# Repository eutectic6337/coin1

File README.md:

# coin1
challenge coin with blinky lights

Feature: Using 8 PWM channels to provide dimming function for 16 LEDs
by connecting pairs in anti-parallel between a PWM pin and a GPIO.

built as a stack of 3 PCBs -
components mounted on top of bottom board,
second board has a cutout to fit a battery and for each mounted component,
and top board has holes to transmit light from LEDs

finished coin to have [relatively] smooth top and bottom

using JLCPCB's serial-number mechanism to put a unique number on each coin

Initial code flashed onto these is
[a modified version of the Arduino Blink demo](software/Blink).

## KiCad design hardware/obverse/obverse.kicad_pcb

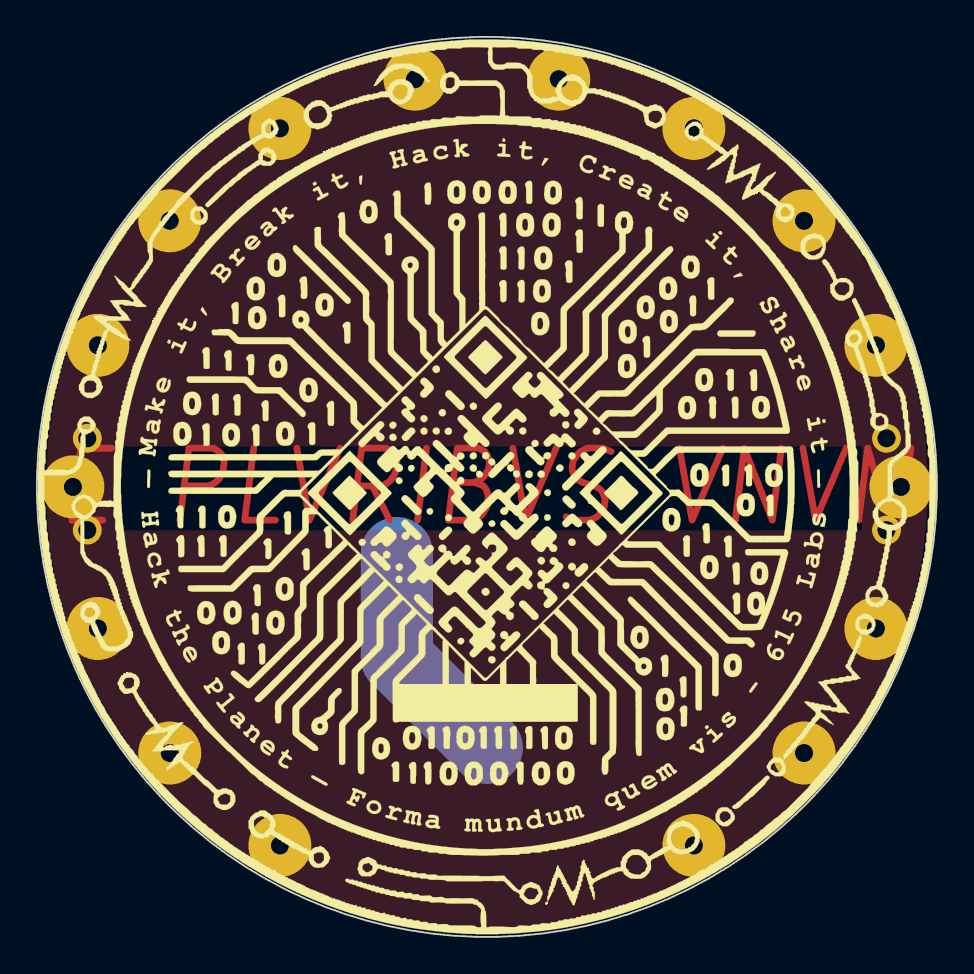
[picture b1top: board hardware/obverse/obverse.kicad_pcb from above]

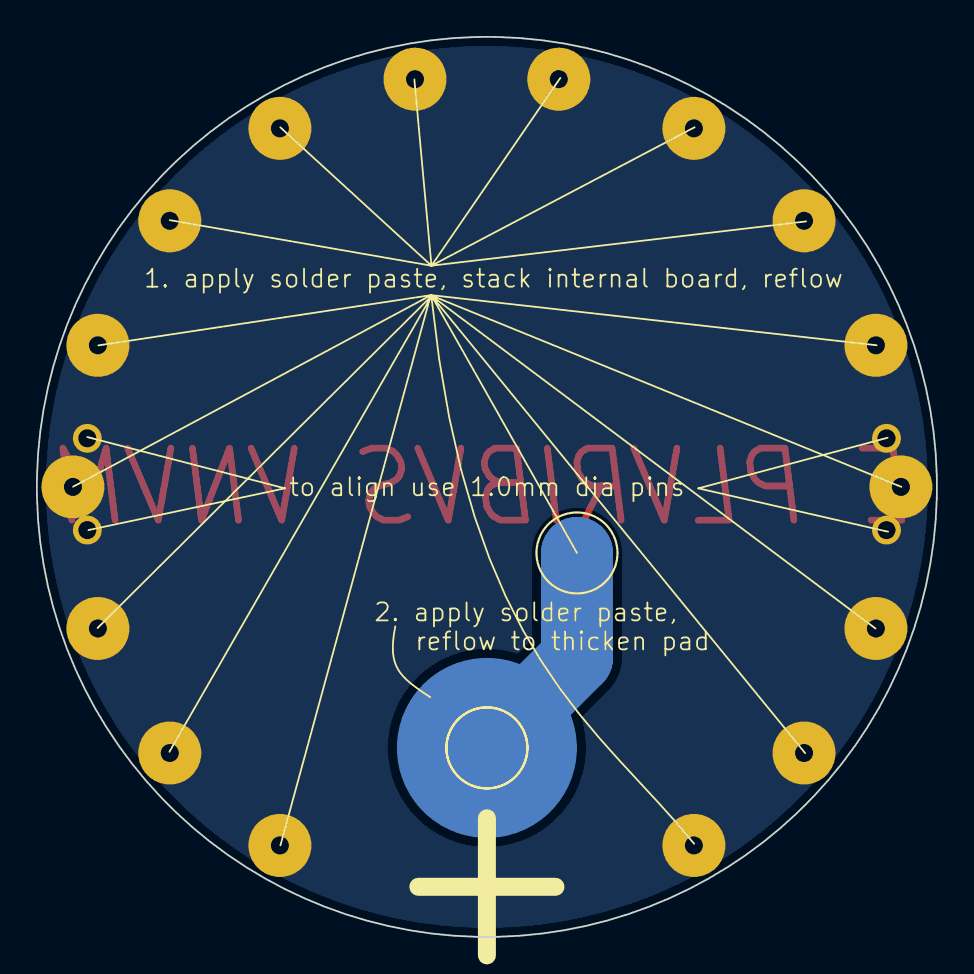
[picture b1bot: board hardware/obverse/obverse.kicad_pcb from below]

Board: 2 copper layers, 50.0 x 50.0 mm, 23 parts (3 on the bottom side), 2 nets.

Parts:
+: BAT+; TestPoint_Pad_D4.0mm
B2: BAT+; TestPoint_Pad_D4.0mm
align-o1, align-o2, align-o3, align-o4: (no value)
aperture-D1, aperture-D2, aperture-D3, aperture-D4, aperture-D5, aperture-D6, aperture-D7, aperture-D8, aperture-D9, aperture-D10, aperture-D11, aperture-D12, aperture-D13, aperture-D14, aperture-D15, aperture-D16: TestPoint_THTPad_D1.0mm_Drill0.5mm
contact-o1: TestPoint_Pad_D4.0mm

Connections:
+3V0: +.1, B2.1, contact-o1.1
GND: align-o1.1, align-o2.1, align-o3.1, align-o4.1, aperture-D1.1, aperture-D2.1, aperture-D3.1, aperture-D4.1, aperture-D5.1, aperture-D6.1, aperture-D7.1, aperture-D8.1, aperture-D9.1, aperture-D10.1, aperture-D11.1, aperture-D12.1, aperture-D13.1, aperture-D14.1, aperture-D15.1, aperture-D16.1

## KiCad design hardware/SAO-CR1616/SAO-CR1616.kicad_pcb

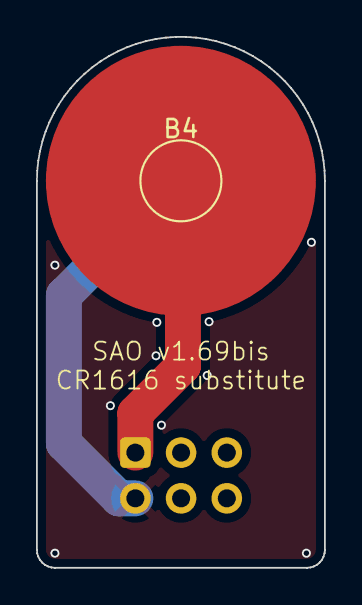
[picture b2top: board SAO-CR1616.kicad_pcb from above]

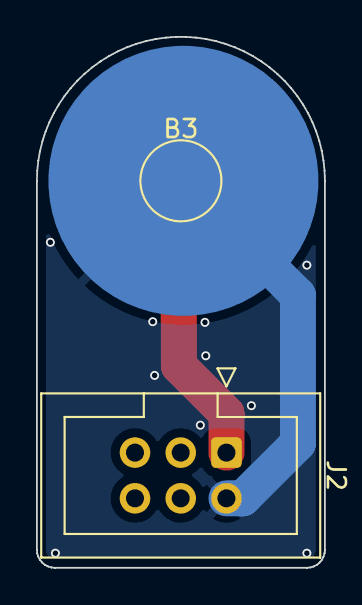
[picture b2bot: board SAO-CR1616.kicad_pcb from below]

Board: 2 copper layers, 16.0 x 29.5 mm, 5 parts (4 on the bottom side), 2 nets.

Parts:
B3: BAT-; TestPoint_Pad_D4.0mm
B4: BAT+; TestPoint_Pad_D4.0mm
J2: SAO v1.69bis addon; IDC-Header_2x03_P2.54mm_Vertical
SAO-P1, SAO-P2: (no value)

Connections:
+3V0: B4.1, J2.1 (3V3), SAO-P1.1
GND: B3.1, J2.2 (GND), SAO-P2.1

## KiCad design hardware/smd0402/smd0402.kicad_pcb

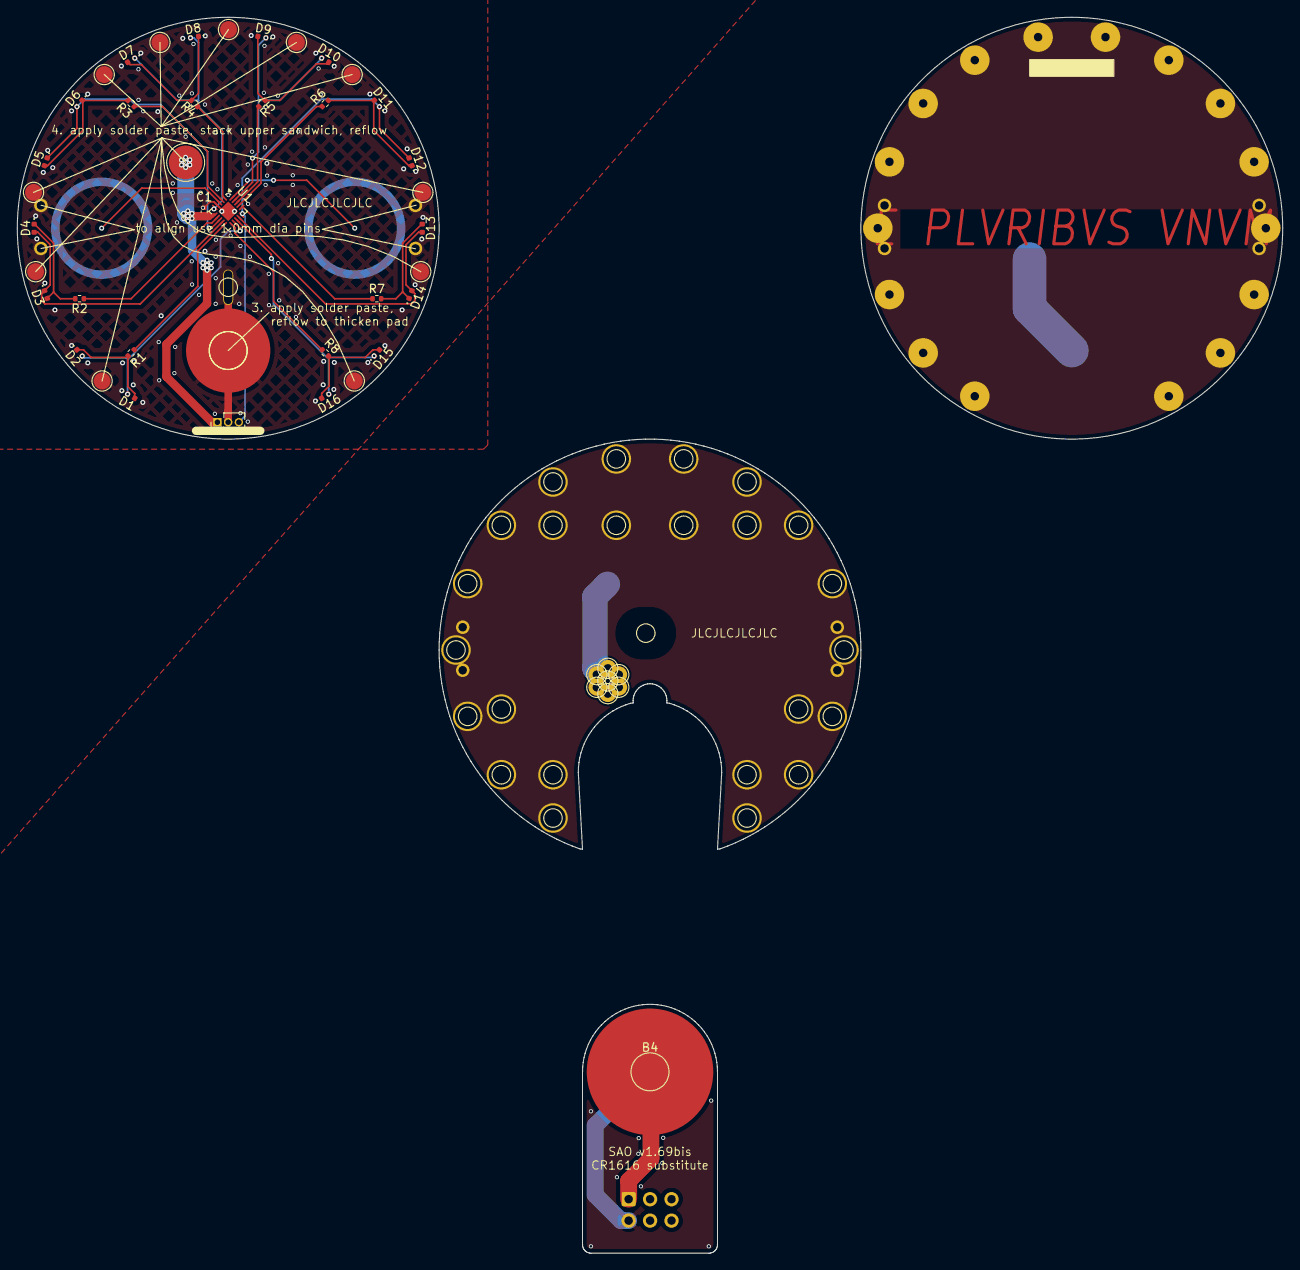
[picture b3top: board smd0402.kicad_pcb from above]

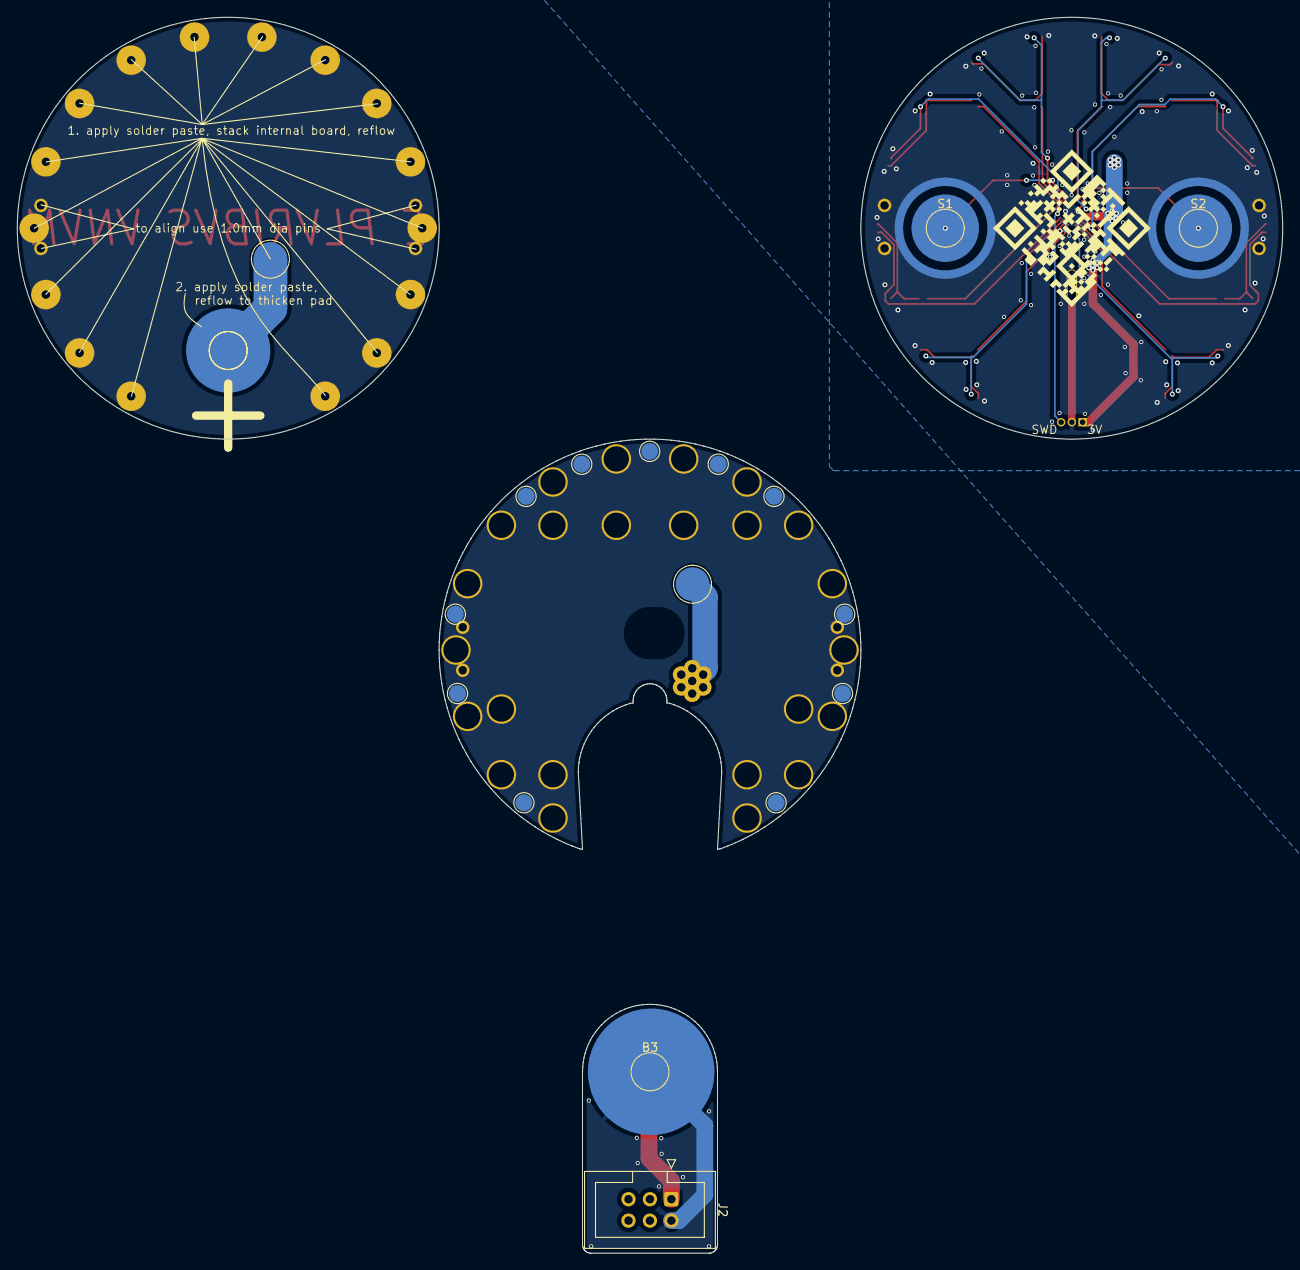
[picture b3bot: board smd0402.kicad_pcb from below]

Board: 2 copper layers, 150.0 x 146.5 mm, 124 parts (21 on the bottom side), 28 nets.

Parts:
+: BAT+; TestPoint_Pad_D4.0mm
-: BAT-; TestPoint_Pad_D4.0mm
B1, B3: BAT-; TestPoint_Pad_D4.0mm
B2, B4: BAT+; TestPoint_Pad_D4.0mm
C1: 1u; C_0402_1005Metric
D1, D2, D3, D4, D5, D6, D7, D8, D9, D10, D11, D12, D13, D14, D15, D16: LED; LED_0402_1005Metric
J1: Conn_01x03; PinHeader_1x03_P1.27mm_Vertical
J2: SAO v1.69bis addon; IDC-Header_2x03_P2.54mm_Vertical
R1, R2, R3, R4, R5, R6, R7, R8: 47R; R_0402_1005Metric
S1, S2: touch; TestPoint_Pad_D4.0mm
SAO-P1, SAO-P2: (no value)
U1: WCH CH32V003F4U6; QFN-20-1EP_3x3mm_P0.4mm_EP1.65x1.65mm
align-i1, align-i2, align-i3, align-i4: (no value)
align-o1, align-o2, align-o3, align-o4: (no value)
align-r1, align-r2, align-r3, align-r4: (no value)
aperture-D1, aperture-D2, aperture-D3, aperture-D4, aperture-D5, aperture-D6, aperture-D7, aperture-D8, aperture-D9, aperture-D10, aperture-D11, aperture-D12, aperture-D13, aperture-D14, aperture-D15, aperture-D16: TestPoint_THTPad_D1.0mm_Drill0.5mm
battery-eject1: TestPoint_THTPad_3.0x3.0mm_Drill1.5mm
clearance-D1, clearance-D2, clearance-D3, clearance-D4, clearance-D5, clearance-D6, clearance-D7, clearance-D8, clearance-D9, clearance-D10, clearance-D11, clearance-D12, clearance-D13, clearance-D14, clearance-D15, clearance-D16: TestPoint_THTPad_3.0x3.0mm_Drill1.5mm
clearance-R1, clearance-R2, clearance-R3, clearance-R4, clearance-R5, clearance-R6, clearance-R7, clearance-R8: TestPoint_THTPad_3.0x3.0mm_Drill1.5mm
clearance-U1: TestPoint_THTPad_3.0x3.0mm_Drill1.5mm
contact-i1: TestPoint_Pad_D4.0mm
contact-o1: TestPoint_Pad_D4.0mm
contact-r1: TestPoint_Pad_D4.0mm
stitch1, stitch1#2, stitch1#3, stitch1#4, stitch1#5, stitch1#6, stitch1#7, stitch1#8, stitch1#9, stitch1#10, stitch1#11, stitch2, stitch2#2, stitch2#3, stitch2#4, stitch2#5, stitch2#6, stitch2#7, stitch2#8, stitch2#9, stitch2#10, stitch2#11: TestPoint_Pad_D2.0mm
through-i1, through-i2, through-i3, through-i4, through-i5, through-i6, through-i7: TestPoint_THTPad_D2.0mm_Drill1.0mm

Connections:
+3V0: +.1, B2.1, B4.1, C1.1, J1.1, J2.1 (3V3), SAO-P1.1, U1.6 (VDD), contact-i1.1, contact-o1.1, contact-r1.1, through-i1.1, through-i2.1, through-i3.1, through-i4.1, through-i5.1, through-i6.1, through-i7.1
/touch1: S1.1, U1.20 (ADC_IN6)
/touch2: S2.1, U1.3 (ADC_IN0)
GND: -.1, B1.1, B3.1, C1.2, J1.2, J2.2 (GND), SAO-P2.1, U1.4 (VSS), U1.21 (VSS), align-i1.1, align-i2.1, align-i3.1, align-i4.1, align-o1.1, align-o2.1, align-o3.1, align-o4.1, align-r1.1, align-r2.1, align-r3.1, align-r4.1, aperture-D1.1, aperture-D2.1, aperture-D3.1, aperture-D4.1, aperture-D5.1, aperture-D6.1, aperture-D7.1, aperture-D8.1, aperture-D9.1, aperture-D10.1, aperture-D11.1, aperture-D12.1, aperture-D13.1, aperture-D14.1, aperture-D15.1, aperture-D16.1, battery-eject1.1, clearance-D1.1, clearance-D2.1, clearance-D3.1, clearance-D4.1, clearance-D5.1, clearance-D6.1, clearance-D7.1, clearance-D8.1, clearance-D9.1, clearance-D10.1, clearance-D11.1, clearance-D12.1, clearance-D13.1, clearance-D14.1, clearance-D15.1, clearance-D16.1, stitch1.1, stitch1#2.1, stitch1#3.1, stitch1#4.1, stitch1#5.1, stitch1#6.1, stitch1#7.1, stitch1#8.1, stitch1#9.1, stitch1#10.1, stitch1#11.1, stitch2.1, stitch2#2.1, stitch2#3.1, stitch2#4.1, stitch2#5.1, stitch2#6.1, stitch2#7.1, stitch2#8.1, stitch2#9.1, stitch2#10.1, stitch2#11.1
GP1: D1.1 (K), D2.2 (A), U1.12 (PC5)
GP2: D3.1 (K), D4.2 (A), U1.9 (PC2)
GP3: D5.1 (K), D6.2 (A), U1.8 (PC1)
GP4: D7.1 (K), D8.2 (A), U1.5 (PD0)
GP5: D9.1 (K), D10.2 (A), U1.19 (PD5)
GP6: D11.1 (K), D12.2 (A), J1.3, U1.15 (SWIO)
GP7: D13.1 (K), D14.2 (A), U1.14 (PC7)
GP8: D15.1 (K), D16.2 (A), U1.13 (PC6)
unnamed: D1.2 (A), D2.1 (K), R1.2
unnamed: D3.2 (A), D4.1 (K), R2.2
unnamed: D5.2 (A), D6.1 (K), R3.2
unnamed: D7.2 (A), D8.1 (K), R4.2
unnamed: D9.2 (A), D10.1 (K), R5.2
unnamed: D11.2 (A), D12.1 (K), R6.2
unnamed: D13.2 (A), D14.1 (K), R7.2
unnamed: D15.2 (A), D16.1 (K), R8.2
PWM1: R1.1, U1.10 (TIM1_CH3)
PWM2: R2.1, U1.7 (TIM2_CH3)
PWM3: R3.1, U1.2 (TIM1_CH2)
PWM4: R4.1, U1.1 (TIM2_CH4)
PWM5: R5.1, U1.18 (TIM2_CH1)
PWM6: R6.1, U1.17 (TIM2_CH2)
PWM7: R7.1, U1.16 (TIM1_CH1)
PWM8: R8.1, U1.11 (TIM1_CH4)

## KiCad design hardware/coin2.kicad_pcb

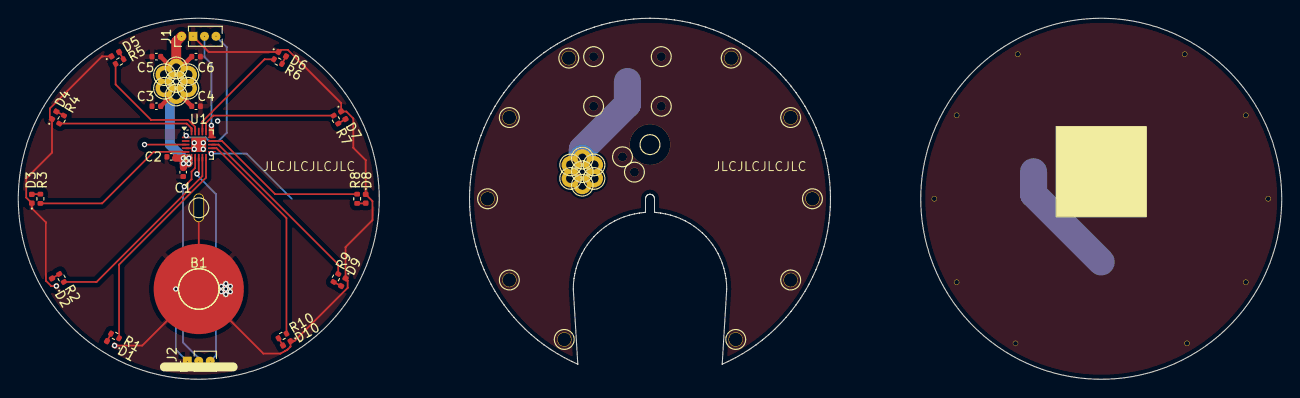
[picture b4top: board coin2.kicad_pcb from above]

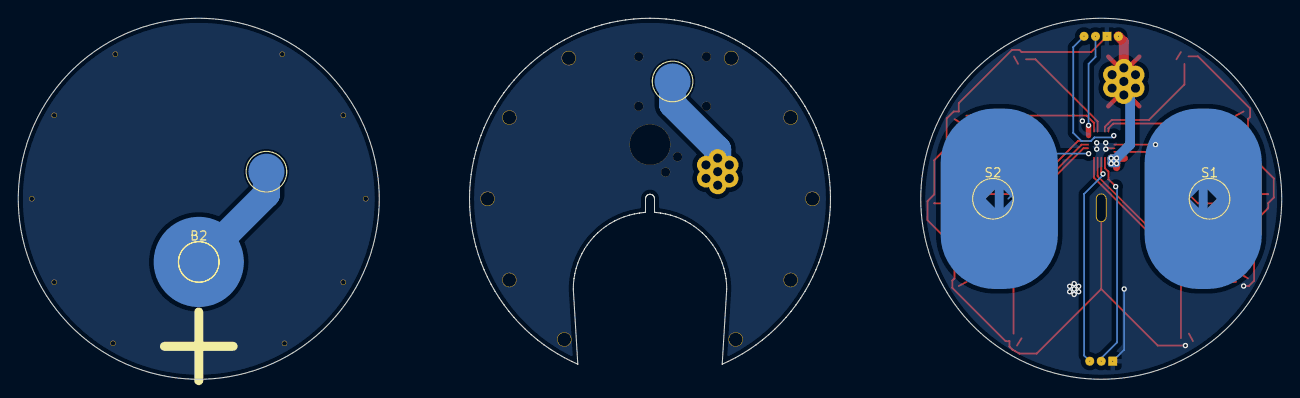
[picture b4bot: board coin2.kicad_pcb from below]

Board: 2 copper layers, 140.0 x 40.0 mm, 77 parts (4 on the bottom side), 28 nets.

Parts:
+: BAT+; TestPoint_Pad_D4.0mm
-: BAT-; TestPoint_Pad_D4.0mm
B1: BAT-; TestPoint_Pad_D4.0mm
B2: BAT+; TestPoint_Pad_D4.0mm
C1, C2, C3, C4, C5, C6: 10n; C_0402_1005Metric
D1, D2, D3, D4, D5, D6, D7, D8, D9, D10: LED; LED_0402_1005Metric
J1: Conn_01x04; PinHeader_1x04_P1.27mm_Vertical
J2: Conn_01x03; PinHeader_1x03_P1.27mm_Vertical
R1, R2, R3, R4, R5, R6, R7, R8, R9, R10: 47R; R_0402_1005Metric
S1, S2: touch; TestPoint_Pad_D4.0mm
T1, T1#2, T12, T13, T14, T15, T16, T18, T19, T20, T21, T21#2, T21#3, T21#4, T21#5, T21#6, T21#7, T22: TestPoint_THTPad_3.0x3.0mm_Drill1.5mm
T42, T43, T44, T45, T46, T48, T49, T50, T51, T52#3: TestPoint_THTPad_D1.0mm_Drill0.5mm
T51#2, T51#3, T51#4, T51#5, T52, T52#2, T53, T53#2, T54, T54#2, T55, T55#2, T56, T56#2: TestPoint_THTPad_D2.0mm_Drill1.0mm
U1: WCH CH32V003F4U6; QFN-20-1EP_3x3mm_P0.4mm_EP1.65x1.65mm

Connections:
+3V0: +.1, B2.1, C1.1, C2.1, C3.1, C4.1, C5.1, C6.1, J1.1, T51#2.1, T51#3.1, T51#4.1, T51#5.1, T52.1, T52#2.1, T53.1, T53#2.1, T54.1, T54#2.1, T55.1, T55#2.1, T56.1, T56#2.1, U1.6 (VDD)
/LED1: R1.1, U1.10 (PC3)
/LED2: R2.1, U1.9 (PC2)
/LED3: R3.1, U1.5 (PD0)
/LED4: R4.1, U1.20 (PD6)
/LED5: R5.1, U1.19 (PD5)
/LED6: R6.1, U1.17 (PD3)
/LED7: R7.1, U1.16 (PD2)
/LED8: R8.1, U1.14 (PC7)
/LED9: R9.1, U1.13 (PC6)
/LED10: R10.1, U1.12 (PC5)
/NRST: J1.4, U1.1 (NRST)
/RX: J2.3, U1.8 (USART_RX_3)
/SWIO: J1.3, U1.15 (SWIO)
/TX: J2.2, U1.7 (USART_TX_3)
/touch1: S1.1, U1.3 (ADC_IN0)
/touch2: S2.1, U1.11 (ADC_IN2)
GND: -.1, B1.1, C1.2, C2.2, C3.2, C4.2, C5.2, C6.2, D1.1 (K), D2.1 (K), D3.1 (K), D4.1 (K), D5.1 (K), D6.1 (K), D7.1 (K), D8.1 (K), D9.1 (K), D10.1 (K), J1.2, J2.1, T1.1, T1#2.1, T12.1, T13.1, T14.1, T15.1, T16.1, T18.1, T19.1, T20.1, T21.1, T21#2.1, T21#3.1, T21#4.1, T21#5.1, T21#6.1, T21#7.1, T22.1, T42.1, T43.1, T44.1, T45.1, T46.1, T48.1, T49.1, T50.1, T51.1, T52#3.1, U1.4 (VSS)
unnamed: D1.2 (A), R1.2
unnamed: D2.2 (A), R2.2
unnamed: D3.2 (A), R3.2
unnamed: D4.2 (A), R4.2
unnamed: D5.2 (A), R5.2
unnamed: D6.2 (A), R6.2
unnamed: D7.2 (A), R7.2
unnamed: D8.2 (A), R8.2
unnamed: D9.2 (A), R9.2
unnamed: D10.2 (A), R10.2

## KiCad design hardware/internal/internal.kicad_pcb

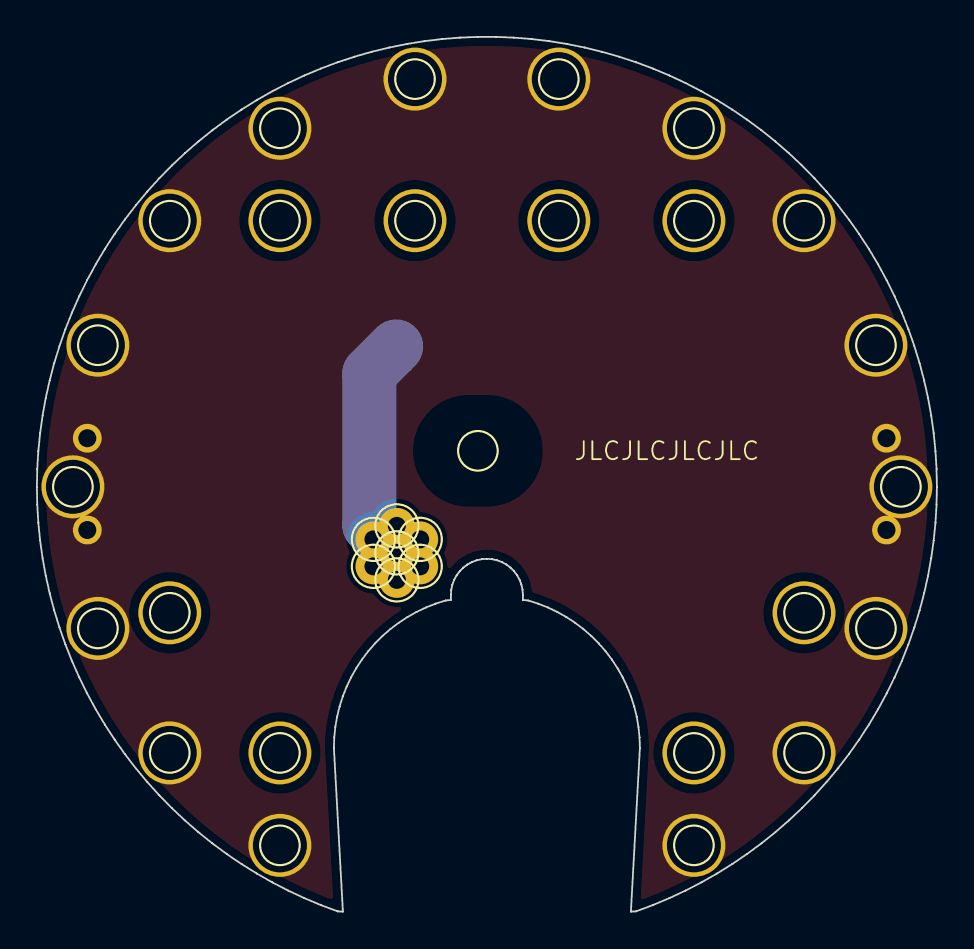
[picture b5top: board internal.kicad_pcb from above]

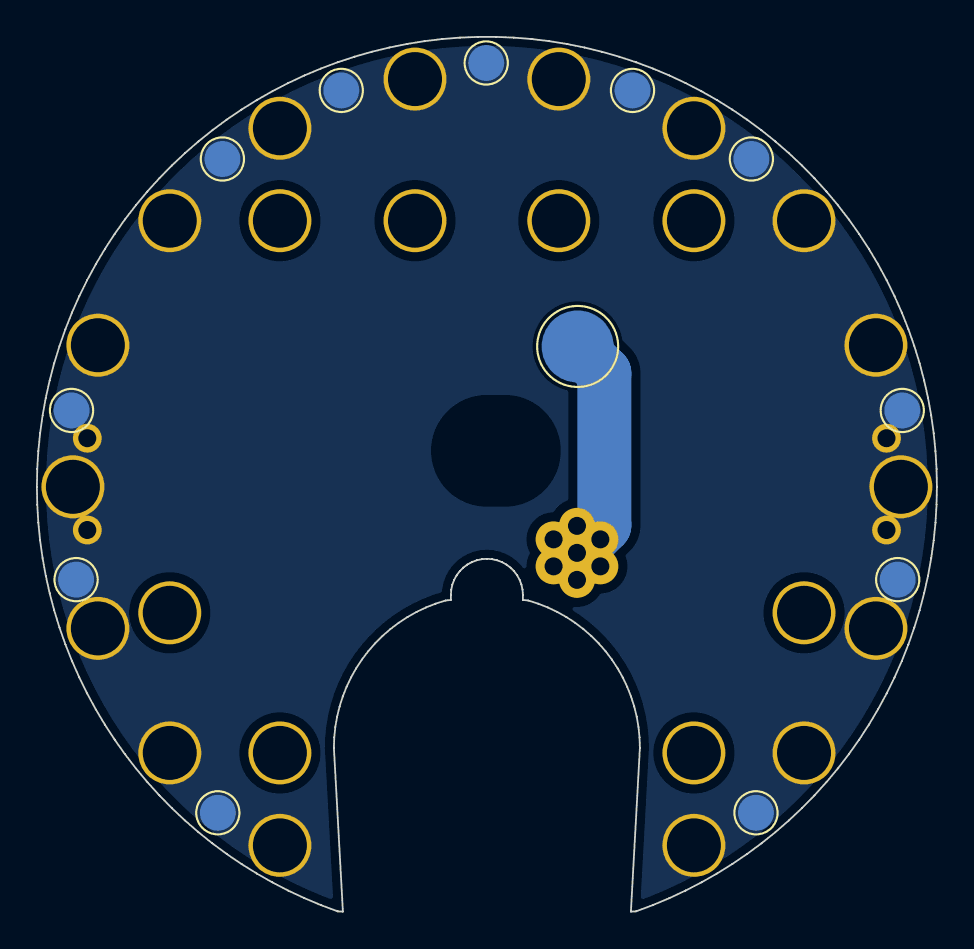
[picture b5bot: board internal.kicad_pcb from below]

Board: 2 copper layers, 50.0 x 48.6 mm, 48 parts (12 on the bottom side), 2 nets.

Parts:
align-i1, align-i2, align-i3, align-i4: (no value)
clearance-D1, clearance-D2, clearance-D3, clearance-D4, clearance-D5, clearance-D6, clearance-D7, clearance-D8, clearance-D9, clearance-D10, clearance-D11, clearance-D12, clearance-D13, clearance-D14, clearance-D15, clearance-D16: TestPoint_THTPad_3.0x3.0mm_Drill1.5mm
clearance-R1, clearance-R2, clearance-R3, clearance-R4, clearance-R5, clearance-R6, clearance-R7, clearance-R8: TestPoint_THTPad_3.0x3.0mm_Drill1.5mm
clearance-U1: TestPoint_THTPad_3.0x3.0mm_Drill1.5mm
contact-i1: TestPoint_Pad_D4.0mm
stitch2, stitch2#2, stitch2#3, stitch2#4, stitch2#5, stitch2#6, stitch2#7, stitch2#8, stitch2#9, stitch2#10, stitch2#11: TestPoint_Pad_D2.0mm
through-i1, through-i2, through-i3, through-i4, through-i5, through-i6, through-i7: TestPoint_THTPad_D2.0mm_Drill1.0mm

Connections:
+3V0: contact-i1.1, through-i1.1, through-i2.1, through-i3.1, through-i4.1, through-i5.1, through-i6.1, through-i7.1
GND: align-i1.1, align-i2.1, align-i3.1, align-i4.1, clearance-D1.1, clearance-D2.1, clearance-D3.1, clearance-D4.1, clearance-D5.1, clearance-D6.1, clearance-D7.1, clearance-D8.1, clearance-D9.1, clearance-D10.1, clearance-D11.1, clearance-D12.1, clearance-D13.1, clearance-D14.1, clearance-D15.1, clearance-D16.1, stitch2.1, stitch2#2.1, stitch2#3.1, stitch2#4.1, stitch2#5.1, stitch2#6.1, stitch2#7.1, stitch2#8.1, stitch2#9.1, stitch2#10.1, stitch2#11.1

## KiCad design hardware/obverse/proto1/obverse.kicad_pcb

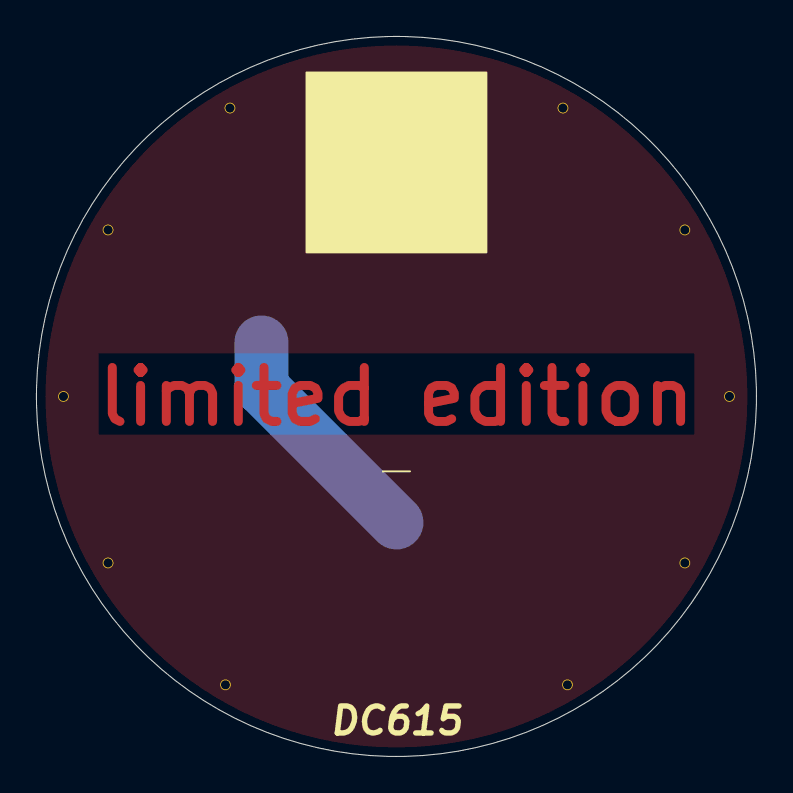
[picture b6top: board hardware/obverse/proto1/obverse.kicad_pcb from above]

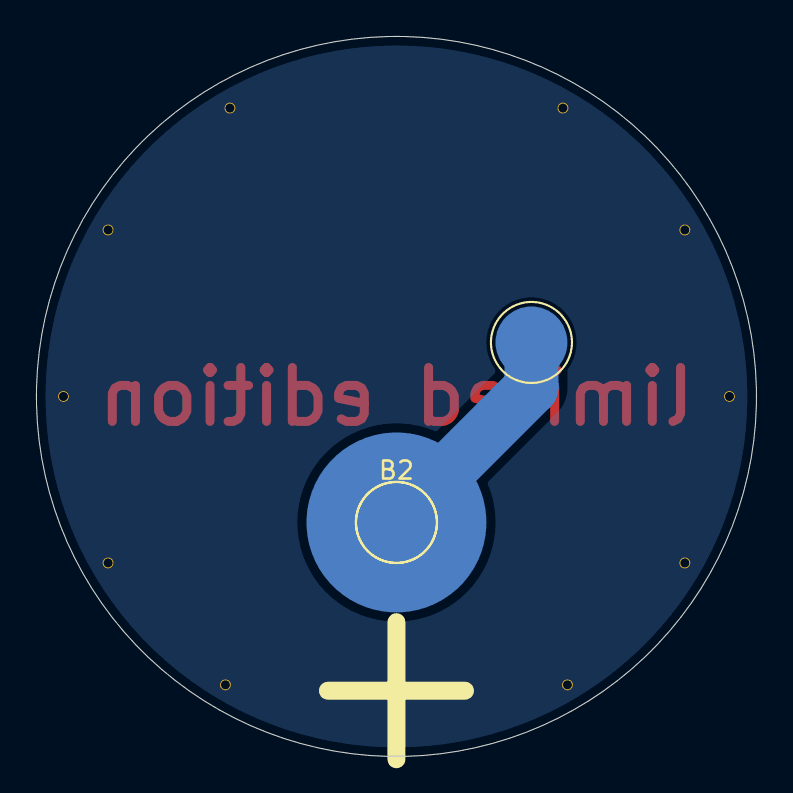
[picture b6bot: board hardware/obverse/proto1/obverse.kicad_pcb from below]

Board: 2 copper layers, 40.0 x 40.0 mm, 12 parts (2 on the bottom side), 2 nets.

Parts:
+: BAT+; TestPoint_Pad_D4.0mm
B2: BAT+; TestPoint_Pad_D4.0mm
T42, T43, T44, T45, T46, T48, T49, T50, T51, T52: TestPoint_THTPad_D1.0mm_Drill0.5mm

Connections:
+3V0: +.1, B2.1
GND: T42.1, T43.1, T44.1, T45.1, T46.1, T48.1, T49.1, T50.1, T51.1, T52.1

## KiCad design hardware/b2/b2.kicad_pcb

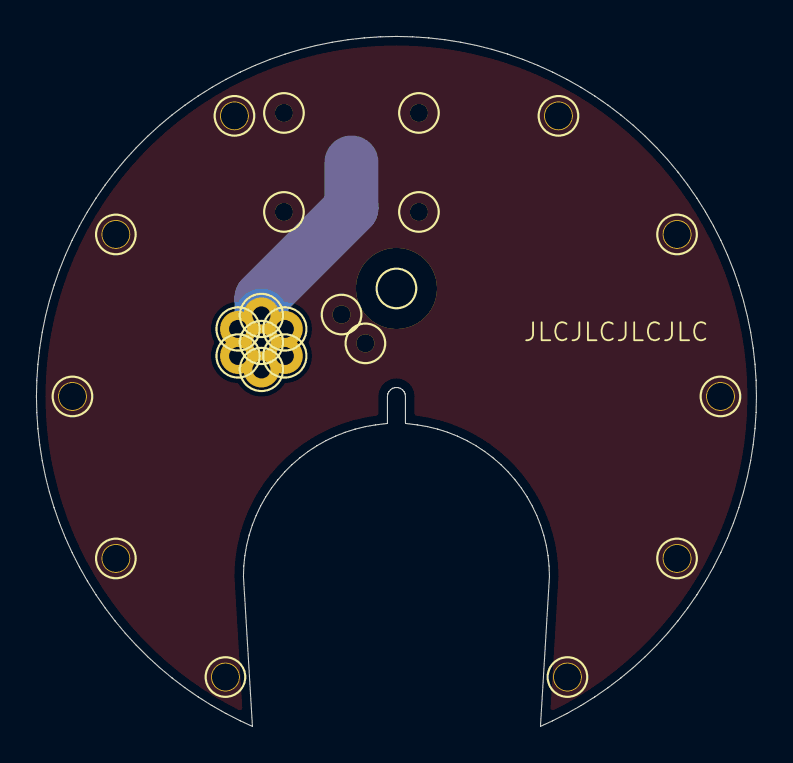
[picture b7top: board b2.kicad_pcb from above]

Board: 2 copper layers, 40.0 x 38.3 mm, 24 parts (0 on the bottom side), 2 nets.

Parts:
T1, T12, T13, T14, T15, T16, T18, T19, T20, T21, T21#2, T21#3, T21#4, T21#5, T21#6, T21#7, T22: TestPoint_THTPad_3.0x3.0mm_Drill1.5mm
T51, T51#2, T52, T53, T54, T55, T56: TestPoint_THTPad_D2.0mm_Drill1.0mm

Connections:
+3V0: T51.1, T51#2.1, T52.1, T53.1, T54.1, T55.1, T56.1
GND: T1.1, T12.1, T13.1, T14.1, T15.1, T16.1, T18.1, T19.1, T20.1, T21.1, T21#2.1, T21#3.1, T21#4.1, T21#5.1, T21#6.1, T21#7.1, T22.1

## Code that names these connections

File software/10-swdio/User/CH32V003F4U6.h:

/*
 * CH32V003F4U6.h
 *
 *  Created on: Apr 29, 2025
 *      Author: mlp
 */

#ifndef USER_CH32V003F4U6_H_
#define USER_CH32V003F4U6_H_

#define PD7 1
#define PA1 2
#define PA2 3
#define VSS 4
#define PD0 5
#define VDD 6
#define PC0 7
#define PC1 8
#define PC2 9
#define PC3 10
#define PC4 11
#define PC5 12
#define PC6 13
#define PC7 14
#define PD1 15
#define PD2 16
#define PD3 17
#define PD4 18
#define PD5 19
#define PD6 20

#if REMAP == 00
#define UCK	PD4
#define A7	PD4
#define OPO	PD4
#define TIM2_ETR	PD4

#define UTX	PD5
#define A5	PD5
#define URX	PD6
#define A6	PD6

#define NRST	PD7
#define OPP1	PD7

#define A1	PA1
#define OPN0	PA1

#define A0	PA2
#define OPP0	PA2
#define TIM1_CH2N	PA2

#define OPN1	PD0
#define TIM1_CH1N	PD0

#define SDA	PC1
#define NSS	PC1

#define SCL	PC2
#define URTS	PC2
#define TIM1_BKIN	PC2

#define MCO	PC4
#define A2	PC4

#define SCK	PC5
#define TIM1_ETR	PC5

#define MOSI	PC6
#define MISO	PC7

#define SWIO	PD1
#define TIM1_CH3N	PD1
#define AETR2	PD1

#define A3	PD2

#define A4	PD3
#define AETR	PD3
#define UCTS	PD3

#define TIM1_CH1	PD2
#define TIM1_CH2	PA1
#define TIM1_CH3	PC3
#define TIM1_CH4	PC4

#define TIM2_CH1	PD4
#define TIM2_CH2	PD3
#define TIM2_CH3	PC0
#define TIM2_CH4	PD7

#elif REMAP == 01
#define TIM1_CH1	PC6
#define TIM1_CH2	PC7
#define TIM1_CH3	PC0
#define TIM1_CH4	PD3

#define TIM2_CH1	PC5
#define TIM2_CH2	PC2
#define TIM2_CH3	PD2
#define TIM2_CH4	PC1

#elif REMAP == 10
#define TIM1_CH1	PD2
#define TIM1_CH2	PA1
#define TIM1_CH3	PC3
#define TIM1_CH4	PC4

#define TIM2_CH1	PC1
#define TIM2_CH2	PD3
#define TIM2_CH3	PC0
#define TIM2_CH4	PD7

#elif REMAP == 11
#define TIM1_CH1	PC4
#define TIM1_CH2	PC7
#define TIM1_CH3	PC5
#define TIM1_CH4	PD4

#define TIM2_CH1	PC1
#define TIM2_CH2	PC7
#define TIM2_CH3	PD6
#define TIM2_CH4	PD5

#else
#error bad REMAP
#endif

#endif /* USER_CH32V003F4U6_H_ */

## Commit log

2024-12-03 add locations for JLCPCB order IDs
2024-12-03 add LCSC part details
2024-12-03 use pin headers for their pads only
2024-12-03 made a version with 0402 rather than 0201 R&D
2024-12-03 route and DRC the new board
2024-12-04 cleanup some hole locations etc.
2024-12-04 add bypass caps, tweak clearance holes
2024-12-05 change connectors from 2.54 to 1.27mm spacing, add decoupling
2024-12-05 separate models and make explicit
2024-12-05 improve DRC
2024-12-05 separate boards, generate fab output
2024-12-05 allow CSVs
2024-12-05 adjust BOM+POS files for JLCPCB
2024-12-05 add LIMITED EDITION text
2024-12-05 make LIMITED EDITION be bare copper
2024-12-05 update fab output
2024-12-05 create QR codes pointing to this repo
2024-12-05 add description
2024-12-05 add repo URL QR on back, tweak text on front
2024-12-05 tweak toward JLC assembly files
2024-12-05 refreshed fab files
2024-12-05 convert KiCad to JLC format
2024-12-05 forgot to nuke unplaced jumpers
2024-12-05 and nuke unused column
2025-01-08 blink 2 LEDs on eval board
2025-01-10 use PD3 for LED, free up PD1 for debug interface
2025-01-10 missed a pin
2025-01-10 also missed initialising GPIOC clock - now it blinks
2025-01-15 use PC3,PC2 = LED1,LED2 on coin
2025-01-15 add coin-chase project
2025-01-15 and rename it
2025-01-15 finish the rename
2025-01-15 ignore packaged fab files
2025-01-15 chase 10 LEDs around the coin
2025-01-17 cleaned up horrible code
2025-01-17 start to make configurable patterns
2025-01-17 new skeleton
2025-01-17 finish the project-rename operation
2025-01-17 Revert "finish the project-rename operation"
    This reverts commit 6e46c28f29a582f192df99f92211d17d19c75442.
2025-01-17 and nuke it
2025-01-18 skeleton for pattern sequence
2025-01-18 add PWM
2025-01-22 [start to] take into account PWM-channel overlaps
2025-01-22 finished pin selection
2025-01-22 add Alchemmer's bunch-o-patterns
2025-01-22 turn on Timer 2's clock
2025-01-22 more cleanup
2025-01-22 add macro to select sequence
2025-02-03 eclipse prefs
2025-02-03 moved clearance holes to match decoupling caps
2025-02-04 reassign touch pads to OPNx
2025-02-04 look long and hard at LED-driving pins
2025-02-04 reassign pins for LEDs and touchpads
2025-02-04 change bypass caps from 10n to 1u
2025-02-06 add some docs on GPIO remapping
2025-02-06 lose NRST, use TIM2 default mapping
2025-02-06 re-route a couple LED signals
2025-02-06 tweak pin allocations
2025-02-12 add some used pins
2025-02-14 boost dia to 50mm, use back-to-back LEDs, add SAO
2025-02-14 document back-to-back LEDs
2025-02-15 clean up DRC
2025-02-15 add via-stitching
2025-02-15 final DRC cleanup
2025-02-16 regenerated repo QR code
2025-02-16 separate boards and generate fab files
2025-02-16 blink a different pair of LEDs
2025-02-16 add diagnostic output
2025-02-16 tweak text out
2025-02-16 verify that what we want the coin to do, it will be able to
2025-02-16 add comments; drop in timer interrupt handler
2025-02-16 use SysTick interrupt to keep time
2025-02-16 convert line endings to all LF
2025-02-16 move defines near to SysTick code
2025-02-16 remove Delay calls
2025-02-17 make clock work(ish)
2025-02-17 make explicit "wait" wrappers
2025-02-22 make inline functions ISO rather than K&R (or C++)
2025-02-22 split main.c into modules
2025-02-22 tweak compiler warning and other options
2025-02-22 rename functions to match files
2025-02-22 start making config switchable
2025-02-22 include prereq header
2025-02-22 call SystemInit()
2025-02-22 add DEBUG build config
2025-02-22 cleanse DEBUG behaviour
2025-02-22 delay before first print, and add blank line
2025-02-22 misc project tweaks
2025-02-22 create ch32fun version of validator
2025-02-22 silence a couple warnings
2025-02-23 further tweaks to get ch32fun project (validate2) to build
2025-02-26 convert to Kicad 9
2025-02-26 add SAO display board
2025-02-26 created board
2025-02-26 added power bypass caps
2025-02-26 separate into fab-able parts
2025-02-26 update fab files
2025-02-26 remove 4 bogus segments from edge cuts
2025-02-26 render boards
2025-02-26 regenerate fab files
2025-02-26 because I moved some text
2025-02-26 regen fab files
2025-02-27 make mousebite holes 0.3mm
2025-02-27 panelize for assembly
2025-04-29 new sample code: first, use SWD for IO
2025-04-29 nuked and recreated
2025-04-29 Eclipse build-parser treats "remove unused section" diagnostic as error?!
2025-04-29 remove "-v" from build stages
2025-04-29 remove link-time extra verbose output
2025-04-29 eliminate format warnings
2025-04-29 enable SWD debug printf
2025-04-29 annotate 2 warnings
2025-04-29 remove calls to USART code
2025-04-29 add ID comment
2025-04-30 define pins
2025-04-30 add pattern-handler
2025-05-20 rename to reflect functionality
2025-05-20 change 'set()/clr()' interface to 'set(val)'
2025-05-21 parameterize pins
2025-05-21 graft in time-handling from ch32fun; also, add assert()s
2025-05-21 cleanup, document
2025-05-21 cleanup
2025-05-22 replace switch/case with table lookup
2025-05-22 extract chip-specific code
2025-05-22 reduce coupling, remove dummy array element
2025-05-22 simplify pin spec
2025-06-03 hash area fill; un-plate MCU clearance hole
2025-06-03 add struct tag
2025-06-09 shrink touchpad to 8mm circle
2025-06-12 add 2 alignment holes to each outer layer
2025-06-12 remove SAO display
2025-06-12 cleanup fab files
2025-06-13 change text
2025-06-13 reduce maskless copper; tweak font
2025-06-13 cleaned up pads; relocated repo QR
2025-06-13 saved
2025-06-13 ready to panelize 4 reverse boards
2025-06-13 integrated final assembly instructions
2025-06-13 tweak instructions
2025-06-13 update rails+mousebites empty panel
2025-06-13 separate boards
2025-06-13 automagic project file updates
2025-06-13 rebuild panel with all SWD ports toward outside
2025-06-14 make clearance-holes less likely to contact
2025-06-14 add SVGs of Alchemmer's artwork
2025-06-15 update parts to those in stock at JLC *now*
2025-06-15 separate sandwich layers to generate fab files
2025-06-15 add reference URL
2025-06-15 add tooling holes; relocate fiducials
2025-06-16 add tooling holes; relocate fiducials; cleanup
2025-06-16 start to panelize reverse layer
2025-06-16 finish panelization
2025-06-17 try lower-poly reverse artwork
2025-06-24 make eject-slot NPTH
2025-06-24 add polarity indicators
2025-07-15 clear out obverse silkscreen ready for updated
2025-07-15 imported the latest obverse graphic
2025-07-15 add some GND via stitching to compensate for NPTH eject slot
2025-07-15 put serial-number block on the coin again
2025-07-17 latest separated fabricated boards
2025-07-17 abstract out the fetching of next pattern in sequence
2025-07-18 make it build
2025-07-18 make random build too; tweak Eclipse build settings
2025-07-27 verify that the timer is actually running and readable
2025-07-27 try to avoid breaking the debug I/O
2025-07-27 tweak diagnostics
2025-08-01 use pin base names
2025-08-01 start port to Arduino IDE
2025-08-01 almost builds under Arduino IDE
2025-08-01 unroll loop into Arduino example, watchim go
2025-08-01 re-roll the loop, still works
2025-08-01 simplify sequence
2025-08-01 down to 1% duty cycle
2025-08-01 set PA1 and 2 as GPIO - from https://www.eevblog.com/forum/microcontrollers/ch32v003-info/msg5713903/#msg5713903
2025-08-01 document how to make more pins usable
2025-08-25 lengthen battery-eject slot
2025-08-25 restore plated-through pads for assembly
2025-08-25 tweak vias around ejecter
2025-08-26 prep for another fab run
2025-09-15 update obverse from DC33 to PN26
2025-09-15 update doc text for new scale
2025-09-15 update obverse
2025-10-05 adjust holes to match production run 2
2025-11-20 tweak chip config to allow *all* GPIOs
2025-11-20 add mention of spiffy design feature
2025-11-20 and here's a picture
2025-11-20 use raw HTML instead of Markdown
2026-04-21 change to conference-agnostic obverse art
2026-05-02 updated mini-panel
2026-05-02 add link to software
2026-05-02 describe demo software
2026-05-02 add programming requirements
2026-05-02 add compiler details
2026-05-02 add the steps
2026-05-06 Update README with WCH repo installation instructions
    Added instructions for installing the unofficial WCH repo and additional notes for using the WCH-LinkE device.
2026-05-15 New coin firmware
    This firmware is meant to start at D1, and at random, non-adjacent LEDs use PWM to look as if the light is jumping from one LED to another.
